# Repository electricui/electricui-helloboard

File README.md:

# Electric UI HelloBoard
This is a tiny USB based evaluation board which makes development against a common platform easier, and helps introduce new users to [Electric UI](https://electricui.com/) who may not have hardware on hand.

## Background

The board is based on the Atmel SAMD21E18 microcontroller, a neat little ARM Cortex M0 core in a compact 32 pin package.

The main goal of the board is to provide a quick and painless development experience to people who might not have played with embedded hardware before.

By including a few interactive components, and leveraging existing supported designs and software, the process should be as user-friendly as possible with no additional hardware/software modifications.

## Specifications

The board is *very* closely related to the [Adafruit Trinket M0](https://www.adafruit.com/product/3500) design, but uses an insertable male USB footprint rather than rely on a USB micro cable. The KiCAD design files, gerbers and PDF's are in `/hardware`.

It includes an ambient light sensor, click button, two capacitive touch pads, and a [APA102-2020 RGB LED](https://cpldcpu.wordpress.com/2014/08/27/apa102/) for the user to interact with, discarding the USB micro connector and some power supply related components on the Trinket.

The micro-controller is suitably capable for it's footprint:

- 256kB Flash memory (program storage)
- 32kB RAM
- 32-bit ARM M0 core running at 48MHz
- Native USB
- Supported by the Arduino IDE, or CircuitPython

The small 'thumb-drive' form factor is intended to make the sticks easy to carry and give away.

## Firmware Examples

The `/firmware` directory has a series of Arduino sketches which provide base examples for interacting with the hardware.

Most [basic and intermediate example sketches](https://github.com/electricui/electricui-embedded/tree/master/examples) in the [`electricui-embedded`](https://github.com/electricui/electricui-embedded) corpus should be directly compatible without modification.

## Flashing Firmware

The Adafruit M0 bootloader is used on this board, which supports the Arduino IDE through BOSSA, and will also enumerate as a USB mass storage device. [Simply dropping any compatible UF2 file](https://learn.adafruit.com/adafruit-feather-m0-express-designed-for-circuit-python-circuitpython/uf2-bootloader-details) on the 'drive' will update the firmware.

### Arduino IDE

The bootloader supports Arduino IDE flashing out of the box.

Install the SAMD and Adafruit SAMD hardware definitions from the *Boards Manager*, as [described in this Adafruit guide](https://learn.adafruit.com/adafruit-trinket-m0-circuitpython-arduino/using-with-arduino-ide).

Select Trinket M0 and the USB device in the Tools dropdown, then just flash the board as normal.

> **Note about Serial.print()**
>
> The Adafruit documentation is incorrect regarding usage of `Serial` vs `SerialUSB`. This hardware does not require `SerialUSB` to be used in sketches, as indicated in the [Adapting Sketches to M0](https://learn.adafruit.com/adafruit-trinket-m0-circuitpython-arduino/adapting-sketches-to-m0). That guide is relevant to other Atmel SAMD boards, but the Trinket just uses `Serial` by default.

### UF2

Plug the USB stick into a compatible computer (Windows, macOS, Linux are all fine), and drop a UF2 file into the root of the `TRINKETBOOT` disk.

### SWD Probe

A SWD programmer is required to burn the boot-loader on new hardware for the first time, but can also be used to burn firmware as part of normal development. Doing this will save some memory normally used by the boot-loader.

While any other Atmel compatible SWD programmer (OpenOCD compatible, Atmel branded, or otherwise) can be used, I used a J-Link on Linux (Solus) to flash the boards for the first time. Programming wires are either soldered on or held in place (the two exposed round pads just above the RGB led), and the JLinkExe tool is used to burn the boot-loader binary as described [in this thread](https://forums.adafruit.com/viewtopic.php?f=57&t=142170) (and below):

1. Build the bootloader by cloning the [adafruit uf2-samdx1 repo](https://github.com/adafruit/uf2-samdx1), then running `make BOARD=trinket_m0` on a *nix system.
2. Connect a compatible JLink programmer.
3. From the `/build/trinket_m0` folder, execute `JLinkExe` which I had installed in `/opt/segger/jlink`.
4. `si 1` to set the programming mode to SWD,
5. `speed 4000` to set programming speed to *4kHz*,
6. `device ATSAMD21E18` for this target,
7. `loadbin bootloader-trinket_m0-v2.0.0-adafruit.9-2-g1e0d553.bin, 0x00000000` to burn the freshly built Trinket M0 bootloader to the base address `0x00000000`.
8. `r` to reset the device,
9. `g` to run the program (though I'd advise just power cycling the target at this point),

## Manufacture & Assembly

[Makerfabs](https://www.makerfabs.com/) produced the boards, but any basic tier fab should work fine. 2.0mm thick FR4 is required to fit in normal sockets, and I'd recommend an ENIG finish as it looks a lot nicer.

The rest of the parts can be ordered from DigiKey or Adafruit (if you pull parts off existing Trinket M0 boards).

Assembly should be done with paste and hot air, or a reflow oven if possible. As this board has some fine pitch parts and 0402 components, its not the easiest board for a beginner to assemble. 

I was able to assemble boards by hand without magnification, so people familiar with 0402 and 0.5mm pitch QFN parts shouldn't have too many issues.

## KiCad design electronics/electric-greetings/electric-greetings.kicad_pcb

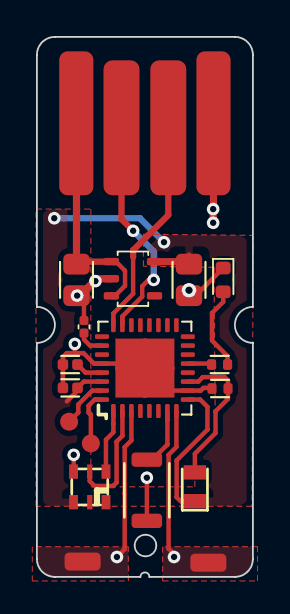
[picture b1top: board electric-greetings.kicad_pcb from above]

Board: 2 copper layers, 12.0 x 30.0 mm, 19 parts (1 on the bottom side), 17 nets.

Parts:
C1, C2: 1u_X5R_1005M; CAPC1005X60N
C3, C4: 10u_X7R_2012M; CAPC2012X110N
D1: LED_RED_1608M; LEDC1608X80L40L
J?1: USB_A_MALE_PCB; USB_A_PLUG_PCB
LOGO1: LOGO; EUI_LOGO_1000X940_MASK
P1, P2: PAD_SOLDER_2mm
Q1: ALS-PT19-315C; TEMT7000X
R1: 1K5_1005M; RESC1005X40N
R2: 10K0_1005M; RESC1005X40N
SL1: SOLDER-LINK-2-TINY; SJ1005-2N
SW1: B3U-1000P_SPST-NO_SMD; B3U-1000P
TEST1, TEST2: PROBE_PAD; TP100
U1: ATSAMD21E18A; QFN33P50_500X500X100L40X24T345N
U2: AP2112K-3.3; SOT95P280X145-5L30L
U3: APA102-2020; AP102_200X200X90L

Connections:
+3.3V: C1.1, C4.1, Q1.C, U1.9, U1.30, U2.5, U3.5
GND: C1.2, C2.2, C3.1, C4.2, D1.C, J?1.4, R2.2, SL1.1, SW1.1, U1.10, U1.28, U2.2, U3.4
LED_CLK: U1.2, U3.3
LED_DATA: U1.1, U3.2
unnamed: C2.1, U1.29
unnamed: D1.A, R1.1
PHOTOSENSOR: Q1.E, R2.1, U1.11
RESET: SL1.2, U1.26
STATUS_LED: R1.2, U1.13
SWD_CLK: TEST1.1, U1.31
SWD_IO: TEST2.1, U1.32
TOUCH_A: P1.1, U1.3
TOUCH_B: P2.1, U1.8
USB_D+: J?1.3, U1.24
USB_D-: J?1.2, U1.23
USER_BUTTON: SW1.2, U1.7
VCC: C3.2, J?1.1, U2.1, U2.3

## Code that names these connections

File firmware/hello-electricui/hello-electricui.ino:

#include <electricui.h>
#include <Adafruit_DotStar.h>
#include <SPI.h>

// Hardware Pin Allocations
#define PIN_BUTTON      4
#define PIN_PHOTOSENSE  2
#define PIN_STATUS      13
#define PIN_TOUCH_A     3
#define PIN_TOUCH_B     0

#define PIN_RGB_DATA    7
#define PIN_RGB_CLOCK   8
#define NUM_PIXELS      1

// RGB LED object
Adafruit_DotStar strip = Adafruit_DotStar(  NUM_PIXELS, 
                                            PIN_RGB_DATA, 
                                            PIN_RGB_CLOCK, 
                                            DOTSTAR_BGR );

typedef struct rgb_t {
  uint8_t r;
  uint8_t g;
  uint8_t b;
};

uint8_t filter_strength = 10;

// Inputs
uint16_t light_adc      = 0;
uint16_t touch_a_adc    = 0;
uint16_t touch_b_adc    = 0;
uint8_t  button_pressed = 0;

// Outputs
uint8_t status_led = 0;
rgb_t dotstar = { 0 };

char device_nickname[16] = "HelloStick Demo";

eui_interface_t usb_cdc;

eui_message_t tracked_variables[] = {
  EUI_UINT16_RO(  "light", light_adc      ),
  EUI_UINT16_RO(  "tA",    touch_a_adc    ),
  EUI_UINT16_RO(  "tB",    touch_b_adc    ),
  EUI_UINT8_RO(   "but",   button_pressed ),

  EUI_UINT8(  "r",    dotstar.r    ),
  EUI_UINT8(  "g",    dotstar.g    ),
  EUI_UINT8(  "b",    dotstar.b    ),


  EUI_UINT8( "filter", filter_strength ),
  EUI_UINT8(    "led", status_led ),
  EUI_CUSTOM(   "rgb", dotstar    ),

  EUI_CHAR_ARRAY( "name", device_nickname ),
};


void setup_pins()
{
  pinMode( PIN_BUTTON,      INPUT_PULLUP  );
  pinMode( PIN_PHOTOSENSE,  INPUT         );
  pinMode( PIN_STATUS,      OUTPUT        );
  pinMode( PIN_TOUCH_A,     INPUT         );
  pinMode( PIN_TOUCH_B,     INPUT         );

  //use the full capability of the ARM M0 ADC
  analogReadResolution(12); 
}

void setup()
{
  Serial.begin( 115200 ); //it's actually USB so baud doesn't matter
  setup_pins();
  
  usb_cdc.output_cb = &usb_write;
  eui_setup_interface( &usb_cdc );
  EUI_TRACK( tracked_variables );

  uint32_t * uuid_buf = get_chip_uuid();  //128-bit UUID
  eui_setup_identifier( (char*)uuid_buf, 16 );

  strip.begin(); 
  strip.show();  // Turn all LEDs off at start
}

void loop()
{
  while( Serial.available() > 0 )  // Process inbound serial data
  {  
    eui_parse( Serial.read(), &usb_cdc );
  }

  // Sample inputs
  touch_a_adc = analogRead( PIN_TOUCH_A );
  touch_b_adc = analogRead( PIN_TOUCH_B );
  button_pressed = !digitalRead( PIN_BUTTON );

  uint16_t raw_light = analogRead( PIN_PHOTOSENSE );
  light_adc = exponential_moving_average( light_adc, raw_light, filter_strength );

  // Control the status LED  
  digitalWrite( PIN_STATUS, status_led );

  //control the RGB led
  strip.setPixelColor( 0, dotstar.r, dotstar.g, dotstar.b );
  strip.show(); 
  
  delay(1);
}

uint16_t exponential_moving_average( uint16_t average, uint16_t input, uint8_t alpha )
{
  if(!alpha)
  {
    alpha = 1;  //0 values will cause divide by 0 errors
  }

  return (average * (alpha-1) + input) / alpha; // running average
}

uint32_t * get_chip_uuid() 
{
  static uint32_t uuid[3] = { 0 };
  uuid[0] = *(volatile uint32_t *)0x0080A00C;
  uuid[1] = *(volatile uint32_t *)0x0080A040;
  uuid[2] = *(volatile uint32_t *)0x0080A044;
  uuid[3] = *(volatile uint32_t *)0x0080A048;
  
  return uuid;
}

// Output function is called by Electric UI
void usb_write( uint8_t *data, uint16_t length )
{
  Serial.write( data, length );
}

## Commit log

2018-07-29 Added base project and started schematic
    Regulation, LEDs, stubs etc done.
2018-07-30 Added atmel microcontroller, notes, layout changes
2018-07-30 Fleshing out schematic. Started PCB shape, placement and cosmetics.
2018-11-10 Schematic tweaks, placement changes, routing
    Most routing done, added capacitive buttons, remapped micro pins slightly.
2018-11-10 More minor tweaks, finished all routing
    Most cosmetics finished, just iterating on useless details now
2018-11-10 Removed usb logo
2018-11-11 Fixed SWD programming points with 1mm pad footprint
2018-12-03 Manufacturing files generated
    Exported gerbers, generated PDF's.
2019-01-28 Cleaned up HW file tree
2019-01-28 Fleshed out readme with basic notes
    Covers rough justification, flashing and software.
2019-01-29 Adds arduino hardware bringup sketch
    Validates hardware functions as intended.
2019-04-20 Started on a Electric UI enabled firmware demo
2019-04-21 Adds user adjustable filter to photosensor values
    Also exposes LED parameters as separate tracked variables.
2020-03-12 Quick sketch for sending hardware values to a UI for graphing
2020-03-12 Readme update, file structure rework
    Also added an image of the hardware!
2020-06-03 Updated hello-electricui firmware
